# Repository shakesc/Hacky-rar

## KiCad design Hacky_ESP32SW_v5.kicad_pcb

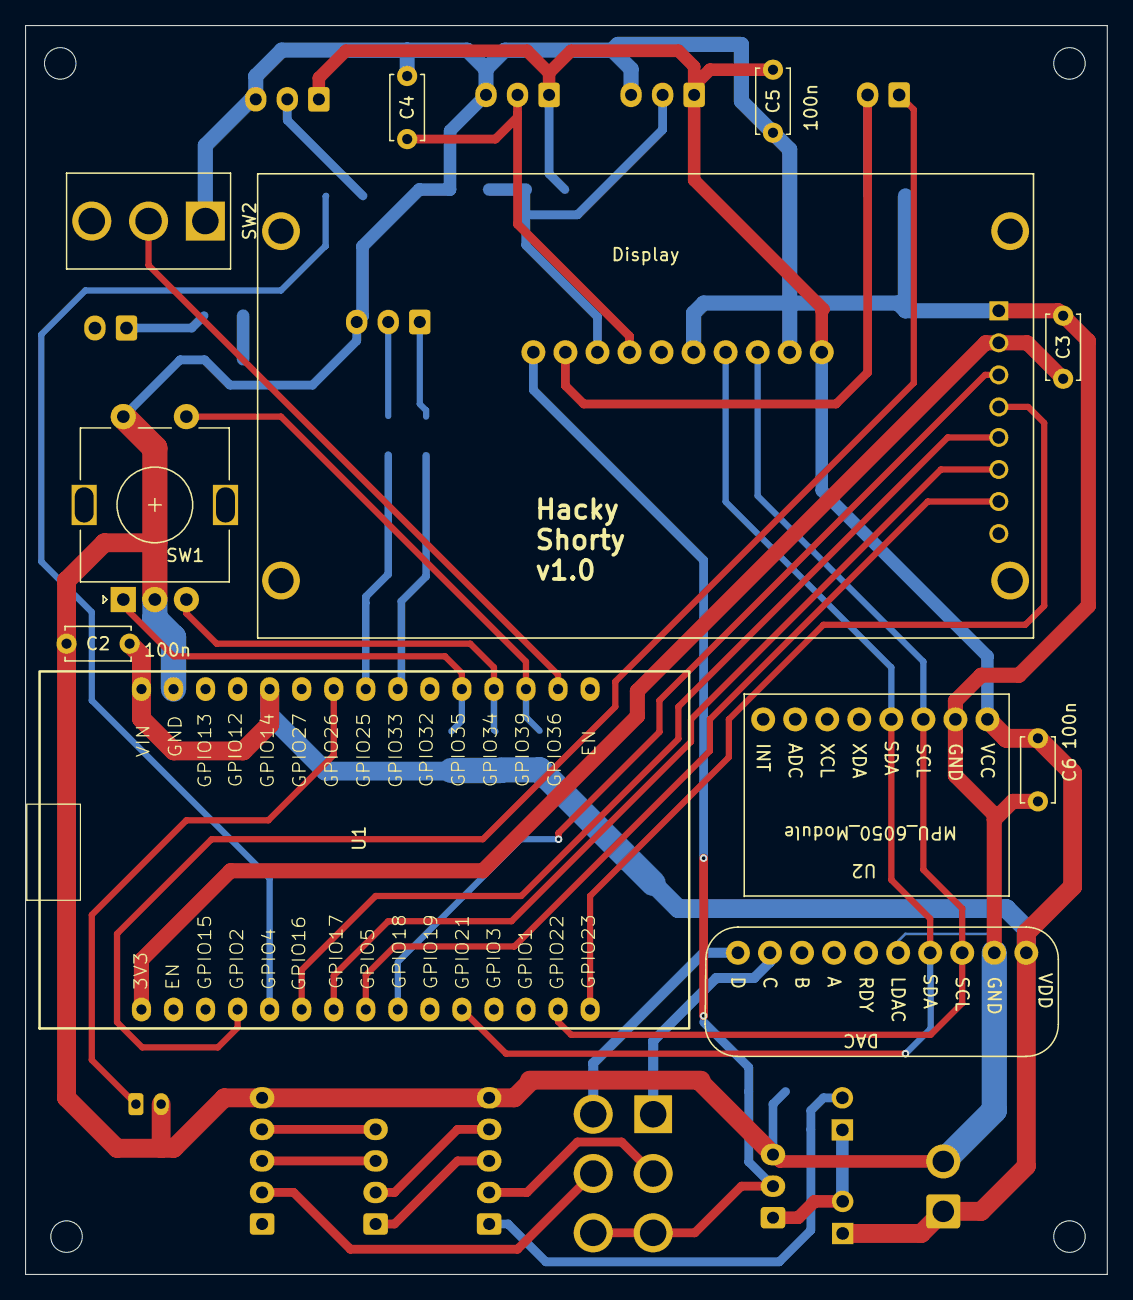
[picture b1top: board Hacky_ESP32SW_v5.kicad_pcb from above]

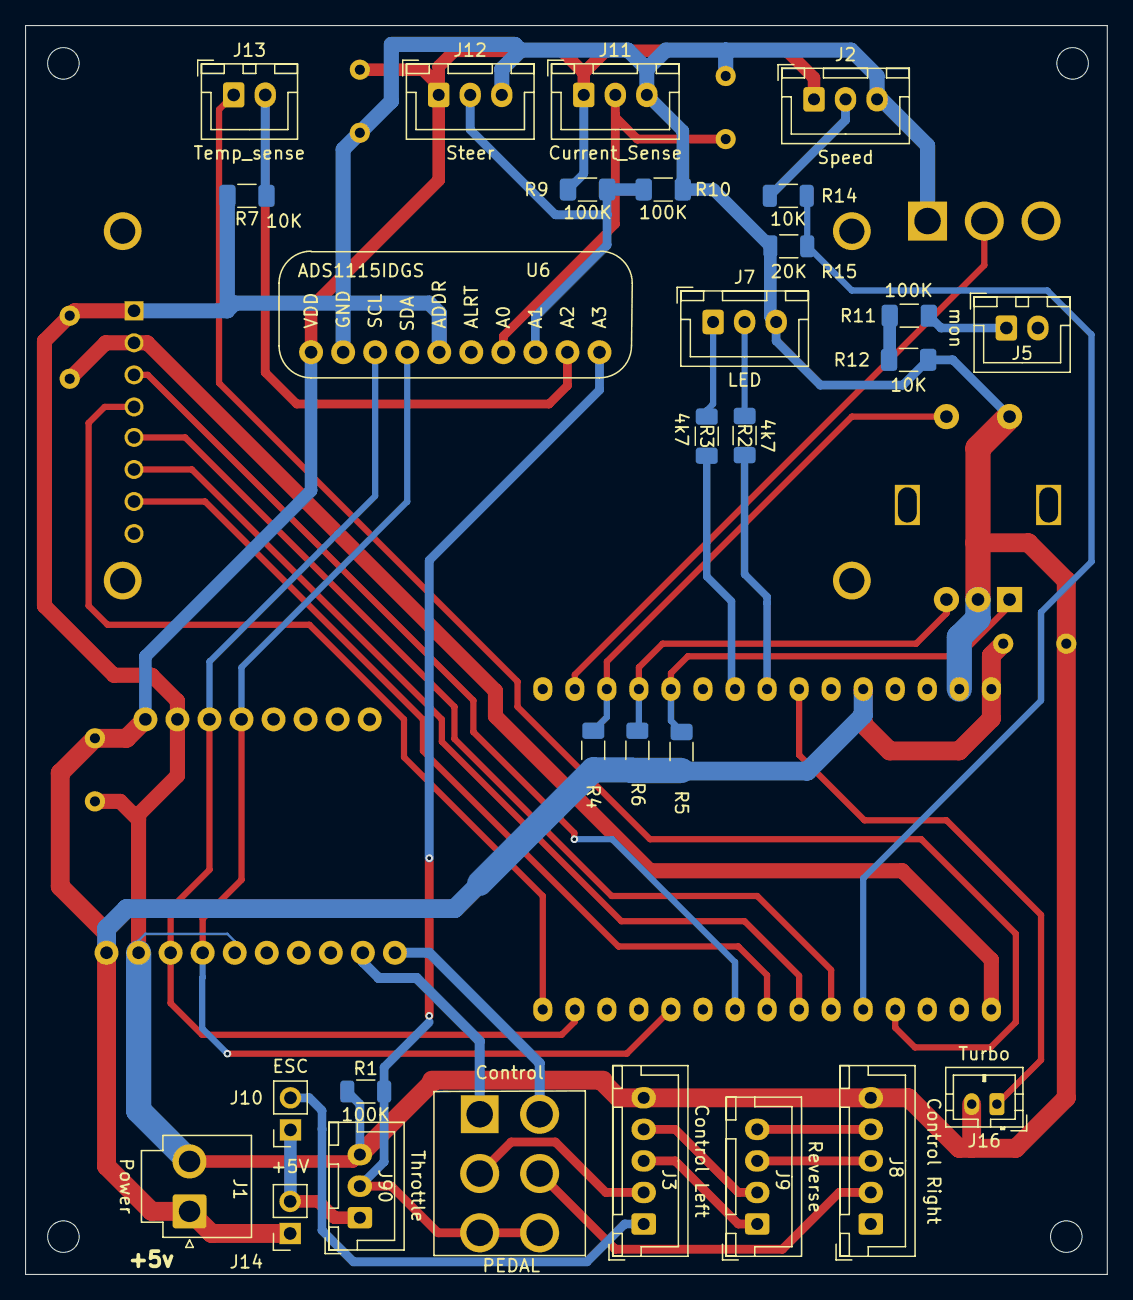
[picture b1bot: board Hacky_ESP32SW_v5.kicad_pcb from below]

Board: 2 copper layers, 85.8 x 99.0 mm, 40 parts (29 on the bottom side), 38 nets.

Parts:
C2, C3, C4, C5, C6: 100n; C_Disc_D5.0mm_W2.5mm_P5.00mm
J1: Power; JST_VH_B2P-VH-B_1x02_P3.96mm_Vertical
J2: Speed; JST_XH_B3B-XH-A_1x03_P2.50mm_Vertical
J3: Control Left; JST_XH_B5B-XH-A_1x05_P2.50mm_Vertical
J5: mon; JST_XH_B2B-XH-A_1x02_P2.50mm_Vertical
J7: LED; JST_XH_B3B-XH-A_1x03_P2.50mm_Vertical
J8: Control Right; JST_XH_B5B-XH-A_1x05_P2.50mm_Vertical
J9: Reverse; JST_XH_B4B-XH-A_1x04_P2.50mm_Vertical
J10: ESC; PinSocket_1x02_P2.54mm_Vertical
J11: Current_Sense; JST_XH_B3B-XH-A_1x03_P2.50mm_Vertical
J12: Steer; JST_XH_B3B-XH-A_1x03_P2.50mm_Vertical
J13: Temp_sense; JST_XH_B2B-XH-A_1x02_P2.50mm_Vertical
J14: +5V; PinSocket_1x02_P2.54mm_Vertical
J16: Turbo; JST_PH_B2B-PH-K_1x02_P2.00mm_Vertical
J90: Throttle; JST_XH_B3B-XH-A_1x03_P2.50mm_Vertical
R1: 100K; R_1206_3216Metric
R2, R3, R4, R5, R6: 4k7; R_1206_3216Metric_Pad1.30x1.75mm_HandSolder
R7, R12: 10K; R_1206_3216Metric_Pad1.30x1.75mm_HandSolder
R9, R10, R11: 100K; R_1206_3216Metric_Pad1.30x1.75mm_HandSolder
R14: 10K; R_1206_3216Metric
R15: 20K; R_1206_3216Metric
SW1: sw1; RotaryEncoder_Alps_EC11E-Switch_Vertical_H20mm
SW2: Ctrl; SW_Slide_SPDT
SW3: PEDAL; SW_Slide_DPDT_larger
U1: ESP32-WROOM-32D; ESP32_WROOM
U2: MPU_6050_Module; MPU-6050
U3: DAC; MCP4728
U5: Display; ST7789V_240x320 BIG
U6: ADS1115IDGS; Adafruit_ADS1115_slim

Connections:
+5V: C2.1, C5.1, C6.1, J1.1, J2.1, J11.1, J12.1, J14.1, R4.2, R5.2, R6.2, R9.1, U1.26 (GPIO14), U1.30 (VIN), U2.1 (VCC), U3.1 (VDD), U6.1 (VDD)
/3V3: C3.1, U1.1 (3V3), U5.2 (VCC_IN)
/CS: U1.8 (GPIO5), U5.7 (CS)
/Current_op: C4.1, J11.2, U6.7 (AIN0)
/DC: U1.7 (GPIO17), U5.6 (DC)
/LED1: R2.1, U1.23 (GPIO25)
/LED2: R3.1, U1.22 (GPIO33)
/MOSI: U1.15 (GPIO23), U5.4 (SDA)
/NTC: J13.2, R7.1, U6.9 (AIN2)
/NTC_feed: J13.1, U1.4 (GPIO2)
/Pedal_feed: J10.1, J14.2, J90.1
/Pedal_in: J90.2, R1.2, SW3.3 (C), SW3.4 (A), U6.10 (AIN3)
/RES: U1.6 (GPIO16), U5.5 (RES)
/RESET: R4.1, SW1.S1, U1.18 (GPIO39)
/Rev_Left_1: J3.3, J9.1
/Rev_Left_2: J3.4, J9.2
/Rev_Right_1: J8.3, J9.3
/Rev_Right_2: J8.4, J9.4
/SCK: U1.9 (GPIO18), U5.3 (SCL)
/SCL: U1.14 (GPIO22), U2.3 (SCL), U3.3 (SCL), U6.3 (SCL)
/SDA: U1.11 (GPIO21), U2.4 (SDA), U3.4 (SDA), U6.4 (SDA)
/Speed_op: R14.2, R15.1, U1.5 (GPIO4)
/Throttle_Control: SW2.2 (B), U1.17 (GPIO36)
/Throttle_in_l: SW3.1 (A), U3.9 (C)
/Throttle_in_r: SW3.6 (C), U3.10 (D)
/Throttle_left: J3.2, SW3.2 (B)
/Throttle_right: J8.2, SW3.5 (B)
/Turbo: J16.1, U1.24 (GPIO26)
/rotA: R5.1, SW1.A, U1.20 (GPIO35)
/rotB: R6.1, SW1.B, U1.19 (GPIO34)
GND: C2.2, C3.2, C4.2, C5.2, C6.2, J1.2, J2.3, J3.5, J7.3, J8.5, J11.3, J12.3, J16.2, J90.3, R1.1, R7.2, R10.2, R12.2, R15.2, SW1.C, SW1.S2, SW2.1 (A), U1.29 (GND), U2.2 (GND), U3.2 (GND), U3.5 (LDAC), U5.1 (GND), U6.2 (GND), U6.5 (ADDR)
unnamed: J2.2, R14.1
unnamed: J5.1, R11.1
unnamed: J7.1, R3.2
unnamed: J7.2, R2.2
unnamed: J3.1, J10.2
unnamed: J12.2, R9.2, R10.1, U6.8 (AIN1)
unnamed: R11.2, R12.1

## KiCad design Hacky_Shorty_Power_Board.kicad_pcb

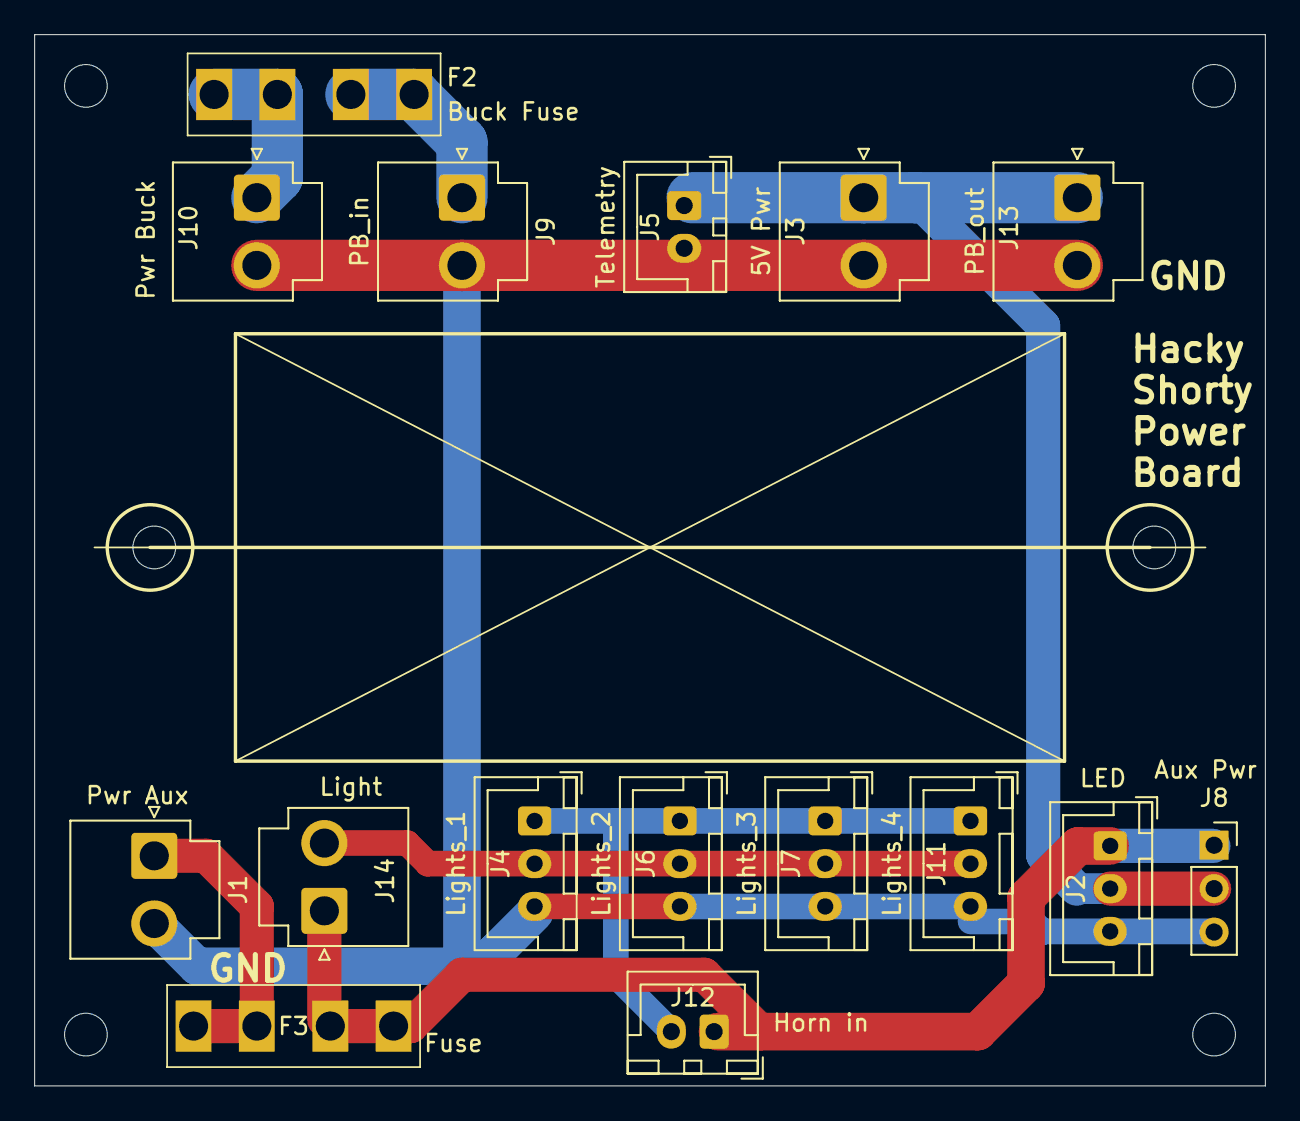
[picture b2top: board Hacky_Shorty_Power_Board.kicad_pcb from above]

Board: 2 copper layers, 72.0 x 61.5 mm, 16 parts (0 on the bottom side), 8 nets.

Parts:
F2: Buck Fuse; Fuse_pcb_micro_Holder
F3: Fuse; Fuse_pcb_micro_Holder
J1: Pwr Aux; JST_VH_B2P-VH-B_1x02_P3.96mm_Vertical
J2: LED; JST_XH_B3B-XH-A_1x03_P2.50mm_Vertical
J3: 5V Pwr; JST_VH_B2P-VH-B_1x02_P3.96mm_Vertical
J4: Lights_1; JST_XH_B3B-XH-A_1x03_P2.50mm_Vertical
J5: Telemetry; JST_XH_B2B-XH-A_1x02_P2.50mm_Vertical
J6: Lights_2; JST_XH_B3B-XH-A_1x03_P2.50mm_Vertical
J7: Lights_3; JST_XH_B3B-XH-A_1x03_P2.50mm_Vertical
J8: Aux Pwr; PinSocket_1x03_P2.54mm_Vertical
J9: PB_in; JST_VH_B2P-VH-B_1x02_P3.96mm_Vertical
J10: Pwr Buck; JST_VH_B2P-VH-B_1x02_P3.96mm_Vertical
J11: Lights_4; JST_XH_B3B-XH-A_1x03_P2.50mm_Vertical
J12: Horn in; JST_XH_B2B-XH-A_1x02_P2.50mm_Vertical
J13: PB_out; JST_VH_B2P-VH-B_1x02_P3.96mm_Vertical
J14: Light; JST_VH_B2P-VH-B_1x02_P3.96mm_Vertical

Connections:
/+5V: J2.2, J3.1, J5.1, J8.2, J13.1
/Horn: J4.1, J6.1, J7.1, J11.1, J12.2
/Light: J4.2, J6.2, J7.2, J11.2, J14.2
/V_power: F3.3, F3.4, J2.1, J8.1, J12.1, J14.1
GND: J1.2, J2.3, J3.2, J4.3, J5.2, J6.3, J7.3, J8.3, J9.2, J10.2, J11.3, J13.2
unnamed: F2.1, F2.2, J10.1
unnamed: F2.3, F2.4, J9.1
unnamed: F3.1, F3.2, J1.1
